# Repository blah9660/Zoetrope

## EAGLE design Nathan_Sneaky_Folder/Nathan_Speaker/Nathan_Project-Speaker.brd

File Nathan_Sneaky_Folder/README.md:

# LED_SPEAKERS
All the code, CAD files, and eagle files that are involved in my project

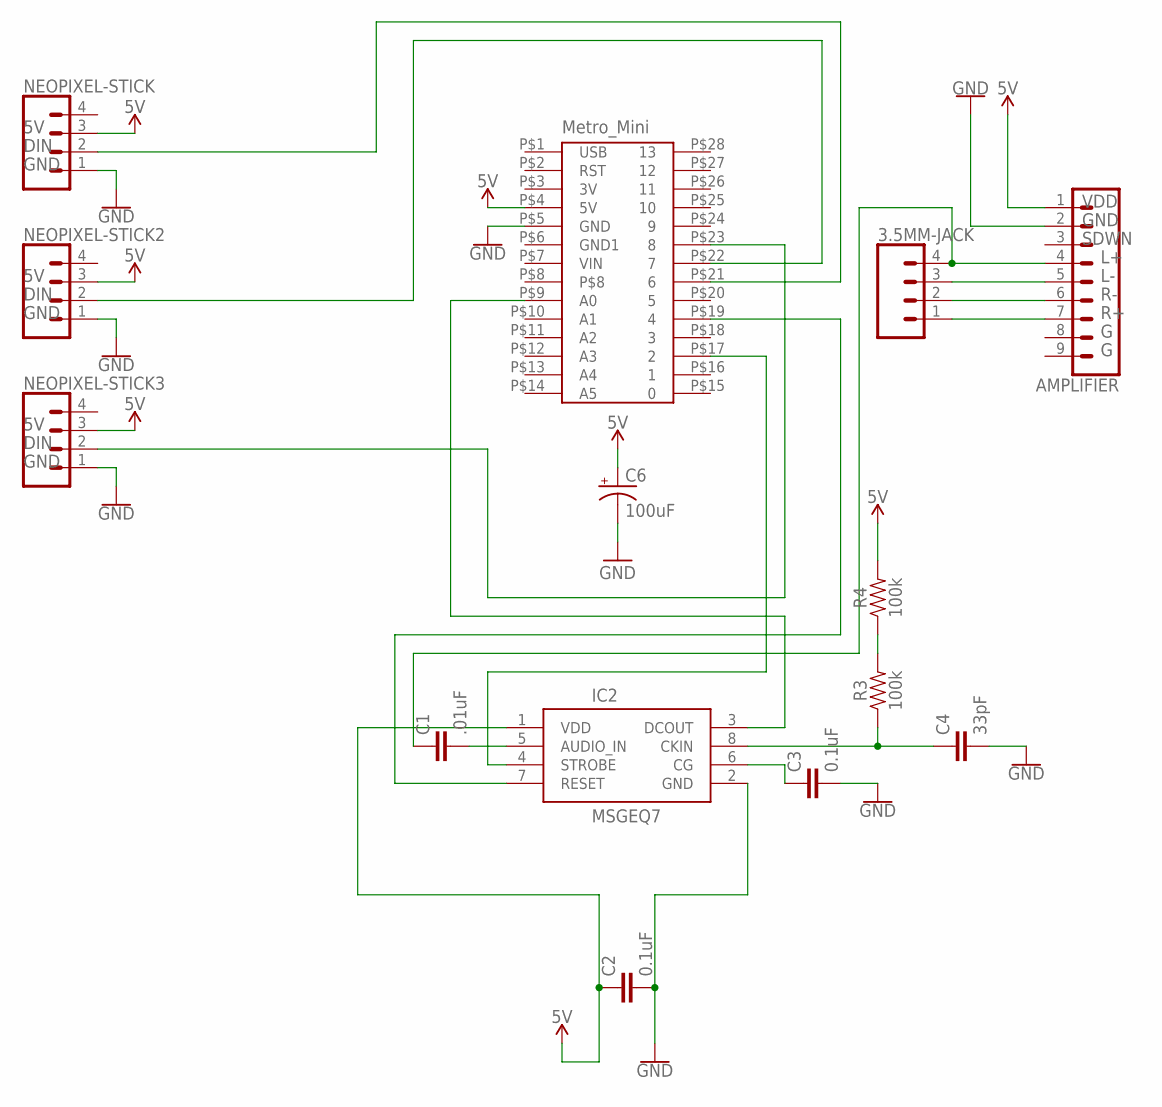
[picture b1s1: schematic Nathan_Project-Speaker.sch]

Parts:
3.5MM-JACK: CONN_04LOCK_LONGPADS; 1X04_LOCK_LONGPADS
AMPLIFIER: CONN_09LOCK-LONGPADS; 1X09_LOCK_LONGPADS
C1: .01uF; C5B2.5
C2, C3: 0.1uF; C5B2.5
C4: 33pF; C5B2.5
C6: 100uF; CPOL-RADIAL-2.5MM-6.5MM
IC2: MSGEQ7P; DIP08
NEOPIXEL-STICK, NEOPIXEL-STICK2, NEOPIXEL-STICK3: CONN_04LOCK_LONGPADS; 1X04_LOCK_LONGPADS
R3, R4: 100k; AXIAL-0.3
U$2: METRO-MINI

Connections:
5V: AMPLIFIER.1, C2.1, C6.1 (+), IC2.1 (VDD), NEOPIXEL-STICK.3, NEOPIXEL-STICK2.3, NEOPIXEL-STICK3.3, R4.P$2 (2), U$2.P$4 (5V)
DIN: NEOPIXEL-STICK.2, U$2.P$21 (6)
GND: AMPLIFIER.2, C2.2, C3.2, C4.2, C6.2 (-), IC2.2 (GND), NEOPIXEL-STICK.1, NEOPIXEL-STICK2.1, NEOPIXEL-STICK3.1, U$2.P$5 (GND)
unnamed: C4.1, IC2.8 (CKIN), R3.P$1 (1)
unnamed: IC2.4 (STROBE), U$2.P$17 (2)
unnamed: NEOPIXEL-STICK3.2, U$2.P$23 (8)
unnamed: 3.5MM-JACK.4, AMPLIFIER.4, C1.1
unnamed: 3.5MM-JACK.3, AMPLIFIER.5
unnamed: 3.5MM-JACK.2, AMPLIFIER.6
unnamed: 3.5MM-JACK.1, AMPLIFIER.7
unnamed: C3.1, IC2.6 (CG)
unnamed: R3.P$2 (2), R4.P$1 (1)
unnamed: C1.2, IC2.5 (AUDIO_IN)
unnamed: IC2.7 (RESET), U$2.P$19 (4)
unnamed: IC2.3 (DCOUT), U$2.P$9 (A0)
unnamed: NEOPIXEL-STICK2.2, U$2.P$22 (7)

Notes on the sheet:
DIN
GND
VDD
SDWN

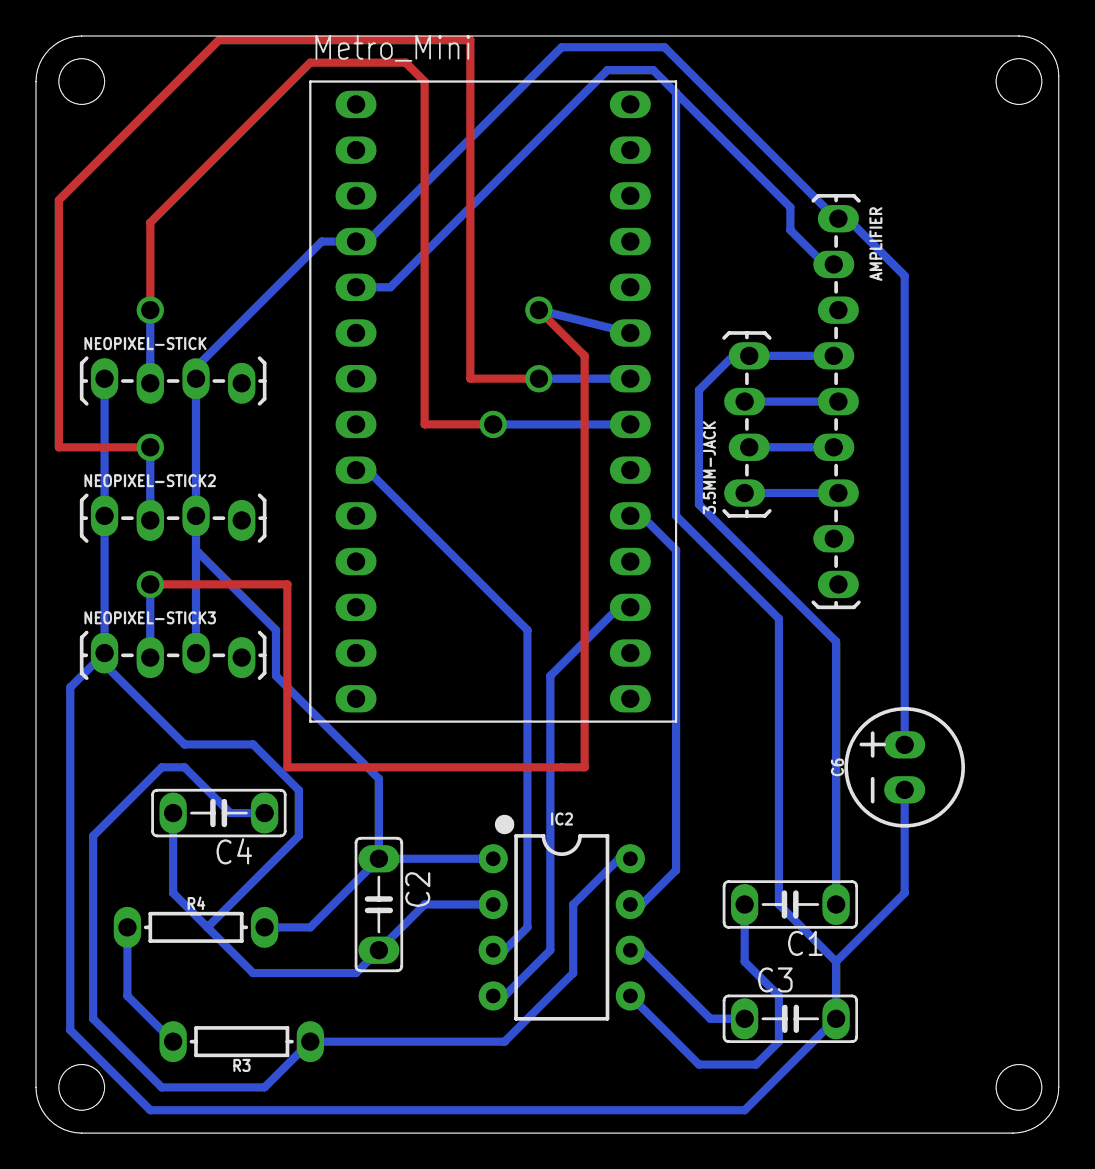
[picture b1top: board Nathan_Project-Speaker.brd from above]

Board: 2 copper layers, 56.8 x 61.0 mm, 14 parts (0 on the bottom side), 16 nets.

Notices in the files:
parts and their libraries:
SparkFun-Connectors: Licensing: Creative Commons ShareAlike 4.0 International - https://creativecommons.org/licenses/by-sa/4.0
